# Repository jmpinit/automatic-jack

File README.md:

# automatic-jack
Hack atoms. Open hardware for nanotechnology.

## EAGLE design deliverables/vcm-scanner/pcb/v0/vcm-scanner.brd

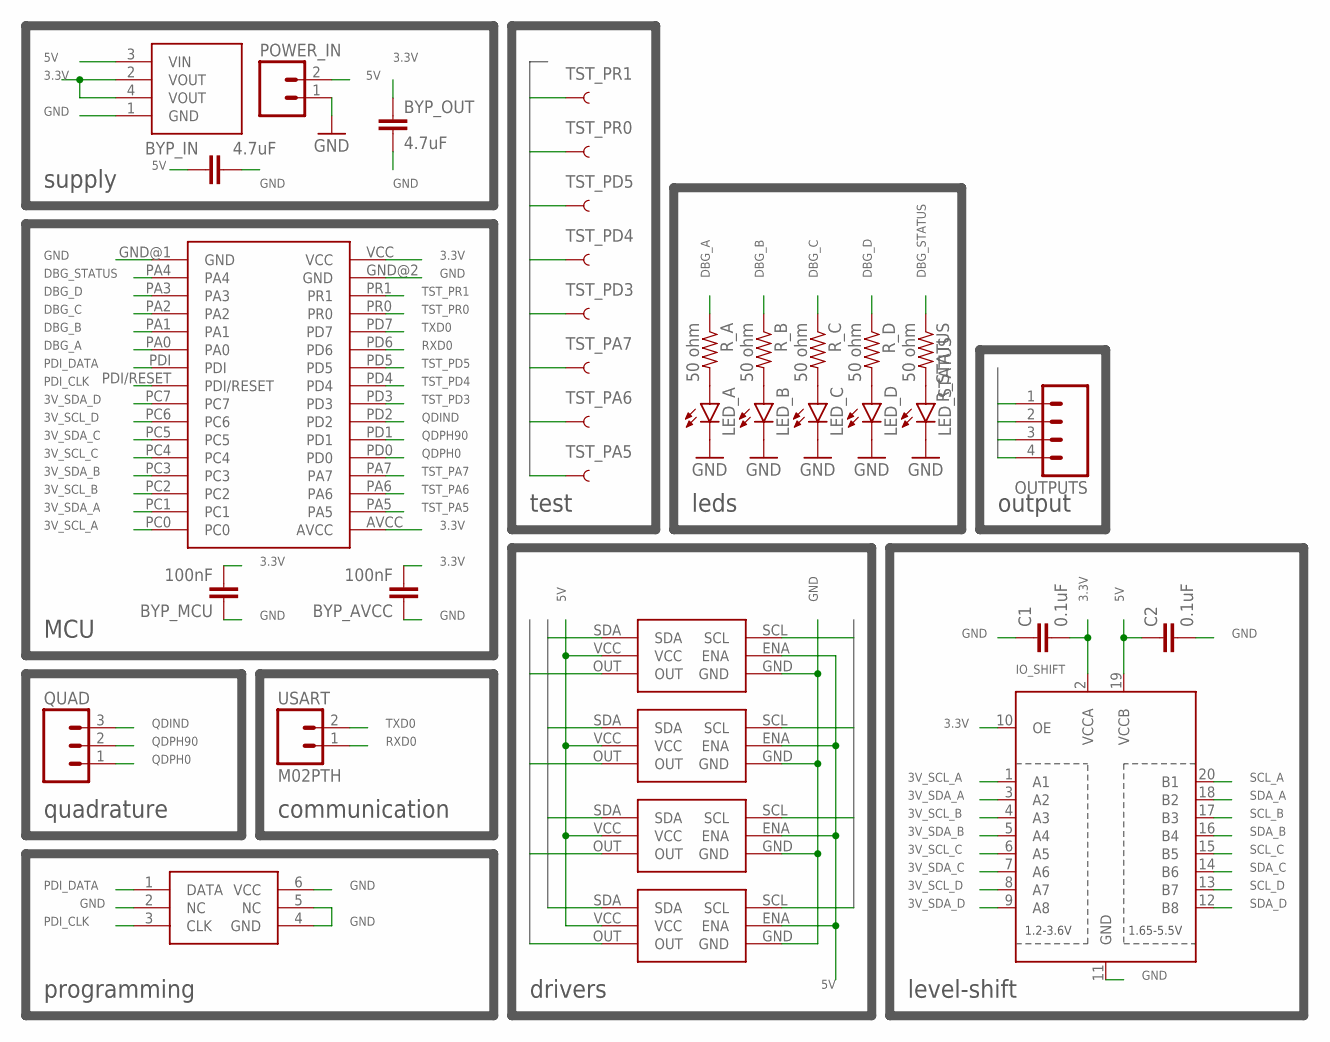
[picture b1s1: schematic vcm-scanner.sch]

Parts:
BYP_AVCC: 100nF; 0603-CAP
BYP_IN: 4.7uF; 0603-CAP
BYP_MCU: 100nF; 0603-CAP
BYP_OUT: 4.7uF; 0603-CAP
C1, C2: 0.1uF; 0603-CAP
DRIVER_A: LV8498CT; LV8498CT-WLP6K
DRIVER_B: LV8498CT; LV8498CT-WLP6K
DRIVER_C: LV8498CT; LV8498CT-WLP6K
DRIVER_D: LV8498CT; LV8498CT-WLP6K
IO_SHIFT: TXB0108PWR; TSSOP20
LED_A: LED0603; LED-0603
LED_B: LED0603; LED-0603
LED_C: LED0603; LED-0603
LED_D: LED0603; LED-0603
LED_STATUS: LED0603; LED-0603
MCU: ATXMEGA8E5-32A
OUTPUTS: M04PTH; 1X04
PDI_PROG: AVR_PDI_PROG; 2X3
POWER_IN: M02PTH; 1X02
QUAD: M03PTH; 1X03
R_A: 50 ohm; 0603-RES
R_B: 50 ohm; 0603-RES
R_C: 50 ohm; 0603-RES
R_D: 50 ohm; 0603-RES
R_STATUS: 50 ohm; 0603-RES
SUPPLY: ZLDO1117; SOT223
TST_PA5, TST_PA6, TST_PA7: TEST-POINT3X5; PAD.03X.05
TST_PD3, TST_PD4, TST_PD5: TEST-POINT3X5; PAD.03X.05
TST_PR0, TST_PR1: TEST-POINT3X5; PAD.03X.05
USART: M02PTH; 1X02

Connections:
3.3V: BYP_AVCC.2, BYP_MCU.2, BYP_OUT.1, C1.2, IO_SHIFT.2 (VCCA), IO_SHIFT.10 (OE), MCU.AVCC, MCU.VCC, SUPPLY.2 (VOUT), SUPPLY.4 (VOUT)
3V_SCL_A: IO_SHIFT.1 (A1), MCU.PC0
3V_SCL_B: IO_SHIFT.4 (A3), MCU.PC2
3V_SCL_C: IO_SHIFT.6 (A5), MCU.PC4
3V_SCL_D: IO_SHIFT.8 (A7), MCU.PC6
3V_SDA_A: IO_SHIFT.3 (A2), MCU.PC1
3V_SDA_B: IO_SHIFT.5 (A4), MCU.PC3
3V_SDA_C: IO_SHIFT.7 (A6), MCU.PC5
3V_SDA_D: IO_SHIFT.9 (A8), MCU.PC7
5V: BYP_IN.1, C2.1, DRIVER_A.ENA, DRIVER_A.VCC, DRIVER_B.ENA, DRIVER_B.VCC, DRIVER_C.ENA, DRIVER_C.VCC, DRIVER_D.ENA, DRIVER_D.VCC, IO_SHIFT.19 (VCCB), POWER_IN.2, SUPPLY.3 (VIN)
DBG_A: MCU.PA0, R_A.1
DBG_B: MCU.PA1, R_B.1
DBG_C: MCU.PA2, R_C.1
DBG_D: MCU.PA3, R_D.1
DBG_STATUS: MCU.PA4, R_STATUS.1
GND: BYP_AVCC.1, BYP_IN.2, BYP_MCU.1, BYP_OUT.2, C1.1, C2.2, DRIVER_A.GND, DRIVER_B.GND, DRIVER_C.GND, DRIVER_D.GND, IO_SHIFT.11 (GND), LED_A.C, LED_B.C, LED_C.C, LED_D.C, LED_STATUS.C, MCU.GND@1 (GND), MCU.GND@2 (GND), PDI_PROG.2 (NC), PDI_PROG.4 (GND), PDI_PROG.5 (NC), PDI_PROG.6 (VCC), POWER_IN.1, SUPPLY.1 (GND)
unnamed: LED_A.A, R_A.2
unnamed: LED_B.A, R_B.2
unnamed: LED_C.A, R_C.2
unnamed: LED_D.A, R_D.2
unnamed: LED_STATUS.A, R_STATUS.2
OUT_A: DRIVER_A.OUT, OUTPUTS.1
OUT_B: DRIVER_B.OUT, OUTPUTS.2
OUT_C: DRIVER_C.OUT, OUTPUTS.3
OUT_D: DRIVER_D.OUT, OUTPUTS.4
PDI_CLK: MCU.PDI/RESET, PDI_PROG.3 (CLK)
PDI_DATA: MCU.PDI, PDI_PROG.1 (DATA)
QDIND: MCU.PD2, QUAD.3
QDPH0: MCU.PD0, QUAD.1
QDPH90: MCU.PD1, QUAD.2
RXD0: MCU.PD6, USART.1
SCL_A: DRIVER_A.SCL, IO_SHIFT.20 (B1)
SCL_B: DRIVER_B.SCL, IO_SHIFT.17 (B3)
SCL_C: DRIVER_C.SCL, IO_SHIFT.15 (B5)
SCL_D: DRIVER_D.SCL, IO_SHIFT.13 (B7)
SDA_A: DRIVER_A.SDA, IO_SHIFT.18 (B2)
SDA_B: DRIVER_B.SDA, IO_SHIFT.16 (B4)
SDA_C: DRIVER_C.SDA, IO_SHIFT.14 (B6)
SDA_D: DRIVER_D.SDA, IO_SHIFT.12 (B8)
TST_PA5: MCU.PA5, TST_PA5.P$1
TST_PA6: MCU.PA6, TST_PA6.P$1
TST_PA7: MCU.PA7, TST_PA7.P$1
TST_PD3: MCU.PD3, TST_PD3.P$1
TST_PD4: MCU.PD4, TST_PD4.P$1
TST_PD5: MCU.PD5, TST_PD5.P$1
TST_PR0: MCU.PR0, TST_PR0.P$1
TST_PR1: MCU.PR1, TST_PR1.P$1
TXD0: MCU.PD7, USART.2

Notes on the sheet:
MCU
drivers
level-shift
quadrature
programming
test
supply
communication
leds
output

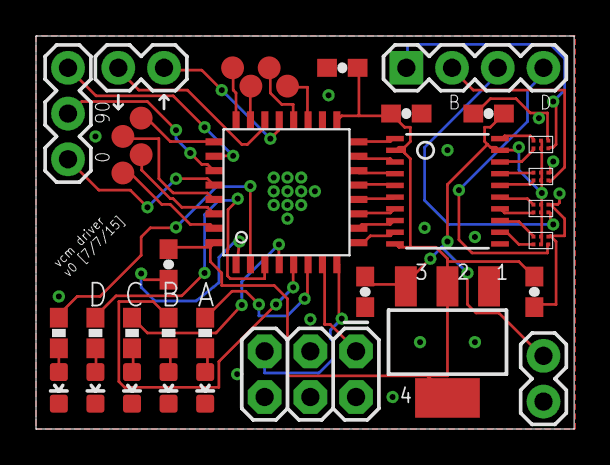
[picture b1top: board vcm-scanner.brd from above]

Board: 2 copper layers, 29.9 x 21.8 mm, 36 parts (0 on the bottom side), 48 nets.

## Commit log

2015-07-07 Basic ignores.
2015-07-07 First draft of overview.
2015-07-07 Basic landing page.
2015-07-07 Format and styling fixes.
2015-07-07 Format fixes.
2015-07-09 VCM scanner PCB v0.
2015-07-20 Added quote for source of name.
2015-07-20 Identified so it can be linked to.

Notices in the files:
parts and their libraries:
SparkFun-Capacitors: Licensing: Creative Commons ShareAlike 4.0 International - https://creativecommons.org/licenses/by-sa/4.0
